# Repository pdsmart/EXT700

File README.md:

# EXT700 - External Expansion Card Adapter for the MZ-700
This project outlines the design of an adapter which allows the Sharp MZ-700 to be used with a single expansion card. 

Normally an MZ-700 would require the MZ-1U06 expansion unit to add expansion cards but these units are as rare as the proverbial rocking-horse excrement!!!

The adapter can be made with a vertical or horizontal MZ-700 expansion card as can be seen here: https://twitter.com/engineerswork1/status/1640438637006553088

Either submit the latest release zip package in releases/ directory to a PCB fabrication plant or contact me as I may have spare.

My website, https://eaw.app will have full build instructions in due course.

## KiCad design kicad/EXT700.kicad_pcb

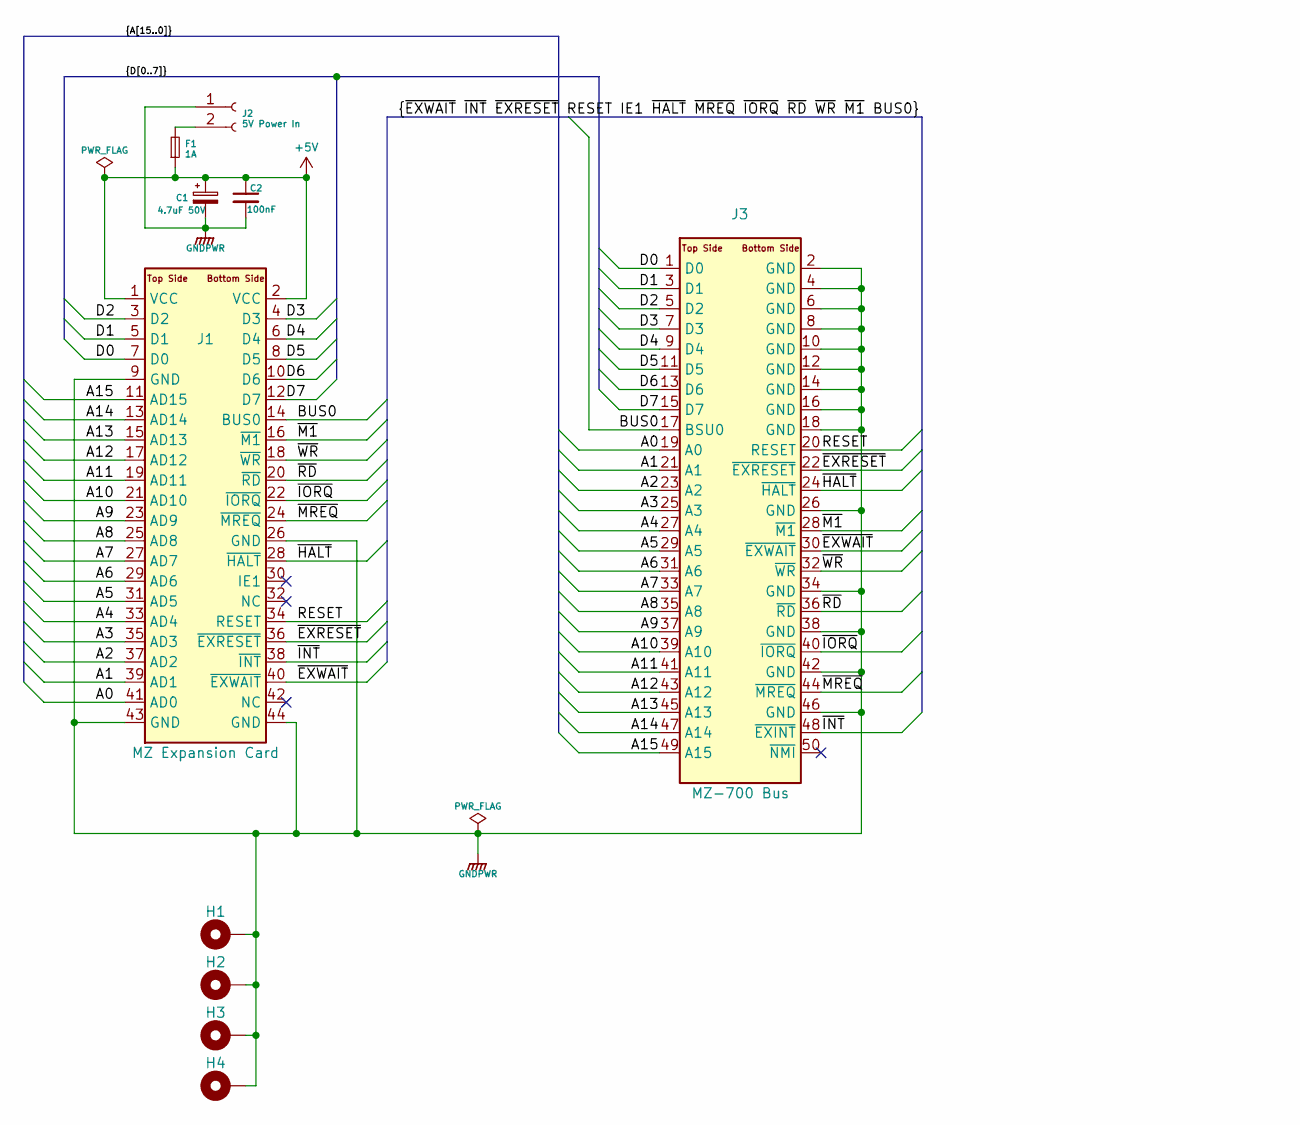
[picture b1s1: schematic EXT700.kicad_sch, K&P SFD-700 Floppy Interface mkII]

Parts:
C1: 4.7uF 50V; CP_Radial_D4.0mm_P2.00mm
C2: 100nF; C_Disc_D5.0mm_W2.5mm_P2.50mm
F1: 1A; Fuse_1210_3225Metric_Pad1.42x2.65mm_HandSolder
H1, H2, H3, H4: MountingHole_Pad; MountingHole_3.2mm_M3_Pad_Via
J1: MZ Expansion Card; EdgeCardConnector_2_54mm_44way
J2: 5V Power In; JST_XH_B2B-XH-AM_1x02_P2.50mm_Vertical
J3: MZ-700 Bus; EdgeCardConnector_2_54mm_50way

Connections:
+5V: C1.1, C2.1, F1.1, J1.1 (VCC), J1.2 (VCC)
/A0: J1.41 (AD0), J3.19 (A0)
/A1: J1.39 (AD1), J3.21 (A1)
/A2: J1.37 (AD2), J3.23 (A2)
/A3: J1.35 (AD3), J3.25 (A3)
/A4: J1.33 (AD4), J3.27 (A4)
/A5: J1.31 (AD5), J3.29 (A5)
/A6: J1.29 (AD6), J3.31 (A6)
/A7: J1.27 (AD7), J3.33 (A7)
/A8: J1.25 (AD8), J3.35 (A8)
/A9: J1.23 (AD9), J3.37 (A9)
/A10: J1.21 (AD10), J3.39 (A10)
/A11: J1.19 (AD11), J3.41 (A11)
/A12: J1.17 (AD12), J3.43 (A12)
/A13: J1.15 (AD13), J3.45 (A13)
/A14: J1.13 (AD14), J3.47 (A14)
/A15: J1.11 (AD15), J3.49 (A15)
/BUS0: J1.14 (BUS0), J3.17 (BSU0)
/D0: J1.7 (D0), J3.1 (D0)
/D1: J1.5 (D1), J3.3 (D1)
/D2: J1.3 (D2), J3.5 (D2)
/D3: J1.4 (D3), J3.7 (D3)
/D4: J1.6 (D4), J3.9 (D4)
/D5: J1.8 (D5), J3.11 (D5)
/D6: J1.10 (D6), J3.13 (D6)
/D7: J1.12 (D7), J3.15 (D7)
/RESET: J1.34 (RESET), J3.20 (RESET)
/~EXRESET: J1.36 (~EXRESET), J3.22 (~EXRESET)
/~EXWAIT: J1.40 (~EXWAIT), J3.30 (~EXWAIT)
/~HALT: J1.28 (~HALT), J3.24 (~HALT)
/~INT: J1.38 (~INT), J3.48 (~EXINT)
/~IORQ: J1.22 (~IORQ), J3.40 (~IORQ)
/~M1: J1.16 (~M1), J3.28 (~M1)
/~MREQ: J1.24 (~MREQ), J3.44 (~MREQ)
/~RD: J1.20 (~RD), J3.36 (~RD)
/~WR: J1.18 (~WR), J3.32 (~WR)
GNDPWR: C1.2, C2.2, H1.1, H2.1, H3.1, H4.1, J1.9 (GND), J1.26 (GND), J1.43 (GND), J1.44 (GND), J2.1, J3.2 (GND), J3.4 (GND), J3.6 (GND), J3.8 (GND), J3.10 (GND), J3.12 (GND), J3.14 (GND), J3.16 (GND), J3.18 (GND), J3.26 (GND), J3.34 (GND), J3.38 (GND), J3.42 (GND), J3.46 (GND)
unnamed: F1.2, J2.2

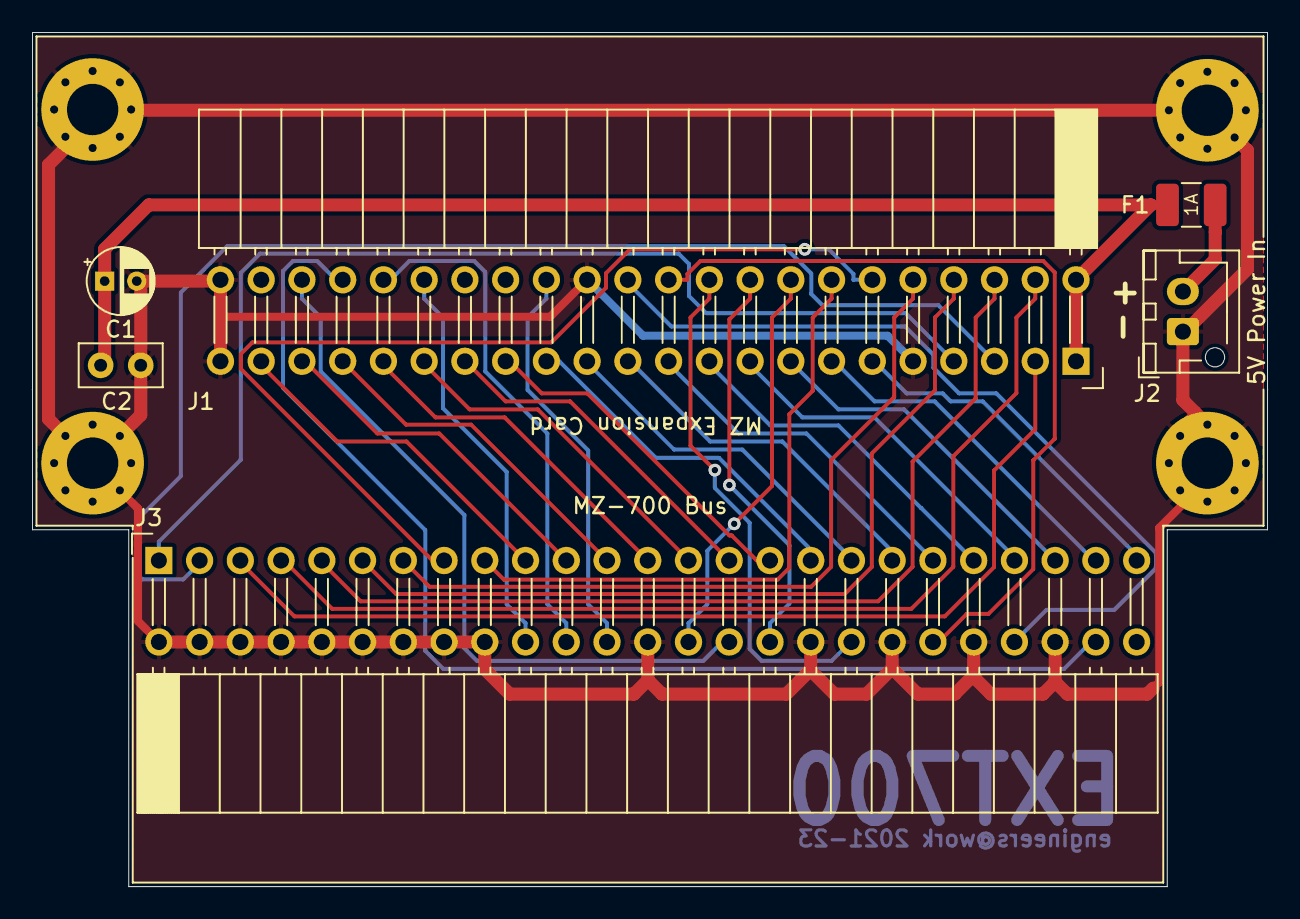
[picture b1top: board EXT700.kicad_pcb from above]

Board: 2 copper layers, 77.0 x 53.2 mm, 10 parts (0 on the bottom side), 38 nets.

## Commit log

2023-04-18 Repo setup
2023-04-18 First release
